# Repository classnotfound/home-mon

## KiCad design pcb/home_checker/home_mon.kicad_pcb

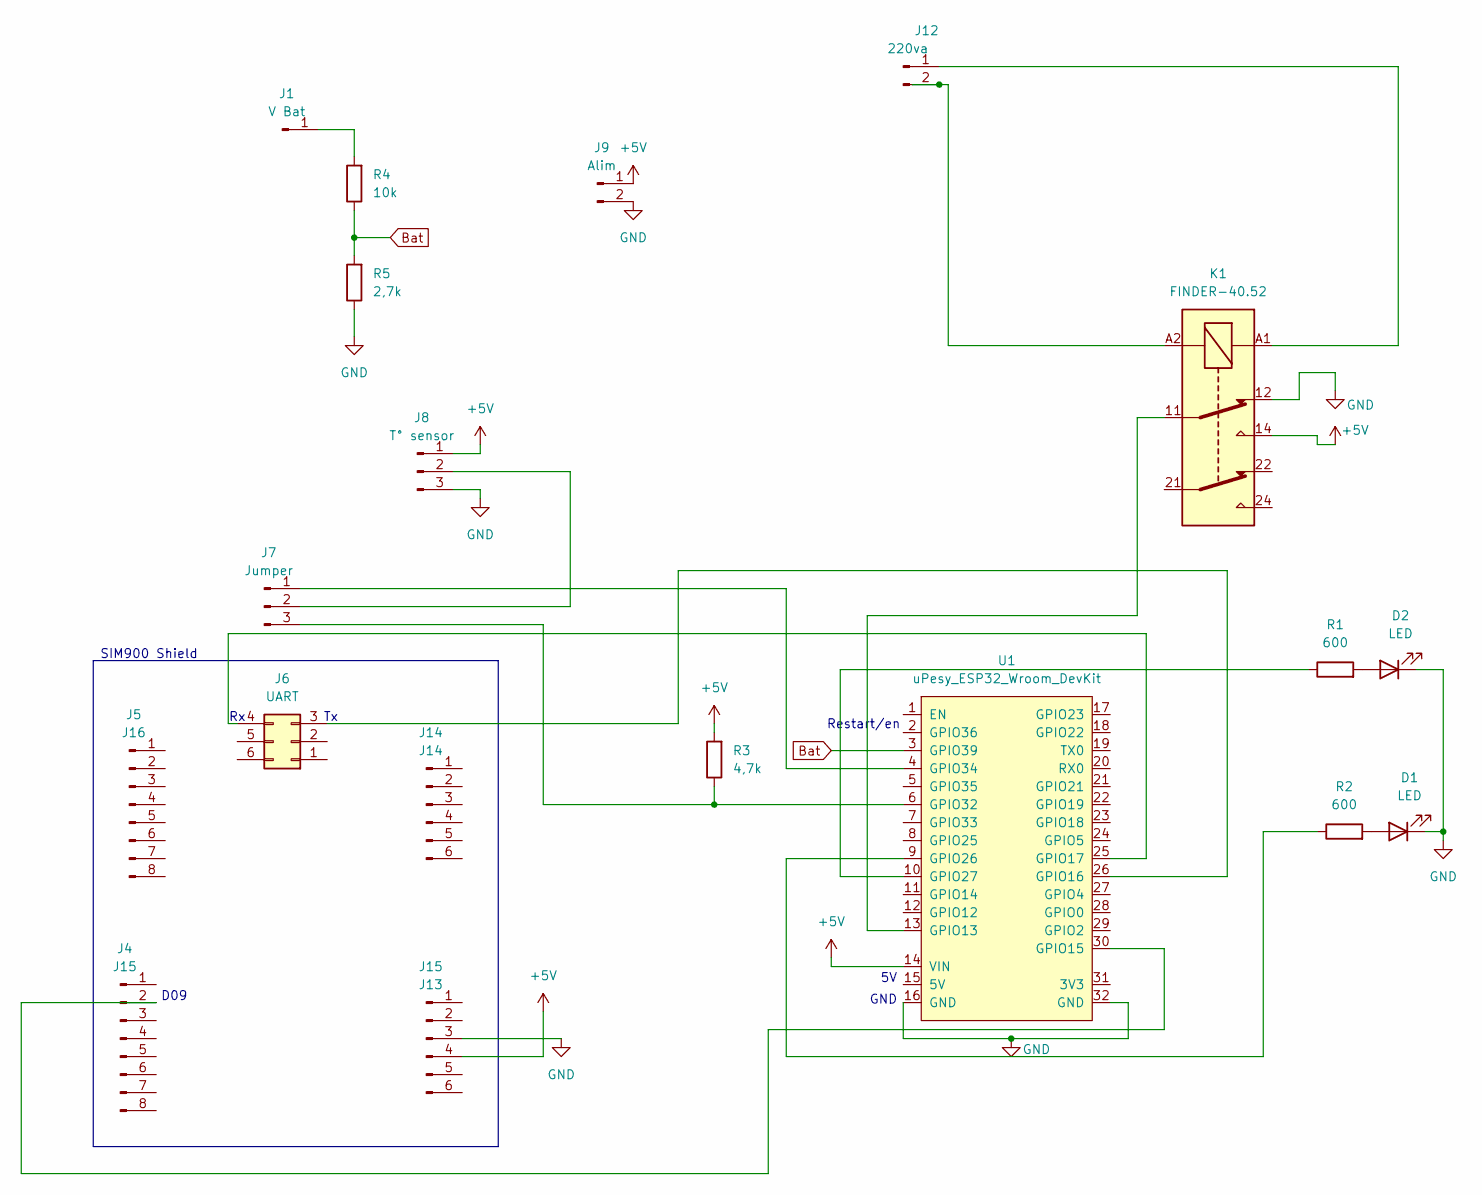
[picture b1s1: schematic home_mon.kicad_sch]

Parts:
D1, D2: LED; LED_D3.0mm
J1: V Bat; TestPoint_Loop_D1.80mm_Drill1.0mm_Beaded
J4: J15; PinHeader_1x08_P2.54mm_Vertical
J5: J16; PinHeader_1x08_P2.54mm_Vertical
J6: UART; PinHeader_2x03_P2.54mm_Vertical
J7: Jumper; PinHeader_1x03_P2.54mm_Vertical
J8: T° sensor; Samtec_HPM-03-01-x-S_Straight_1x03_Pitch5.08mm
J9: Alim; Samtec_HPM-02-01-x-S_Straight_1x02_Pitch5.08mm
J12: 220va; Samtec_HPM-02-01-x-S_Straight_1x02_Pitch5.08mm
J14: J14; PinHeader_1x06_P2.54mm_Vertical
J15: J13; PinHeader_1x06_P2.54mm_Vertical
K1: FINDER-40.52; Relay_DPDT_Finder_40.52
R1, R2: 600; R_Axial_DIN0207_L6.3mm_D2.5mm_P10.16mm_Horizontal
R3: 4,7k; R_Axial_DIN0207_L6.3mm_D2.5mm_P10.16mm_Horizontal
R4: 10k; R_Axial_DIN0207_L6.3mm_D2.5mm_P10.16mm_Horizontal
R5: 2,7k; R_Axial_DIN0207_L6.3mm_D2.5mm_P10.16mm_Horizontal
U1: uPesy_ESP32_Wroom_DevKit

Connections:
+5V: J8.1, J9.1, J15.4, K1.14, R3.2, U1.14 (VIN)
Bat: R4.1, R5.2, U1.3 (GPIO39)
GND: D1.1 (K), D2.1 (K), J8.3, J9.2, J15.3, K1.12, R5.1, U1.16 (GND), U1.32 (GND)
unnamed: D1.2 (A), R2.2
unnamed: D2.2 (A), R1.2
unnamed: J1.1, R4.2
unnamed: J4.2, U1.30 (GPIO15)
unnamed: J6.3, U1.26 (GPIO16)
unnamed: J6.4, U1.25 (GPIO17)
unnamed: J7.1, U1.4 (GPIO34)
unnamed: J7.2, J8.2
unnamed: J7.3, R3.1, U1.6 (GPIO32)
unnamed: J12.1, K1.A1
unnamed: J12.2, K1.A2
unnamed: K1.11, U1.13 (GPIO13)
unnamed: R2.1, U1.9 (GPIO26)
unnamed: R1.1, U1.10 (GPIO27)

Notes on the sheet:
Restart/en
D09
SIM900 Shield
GND

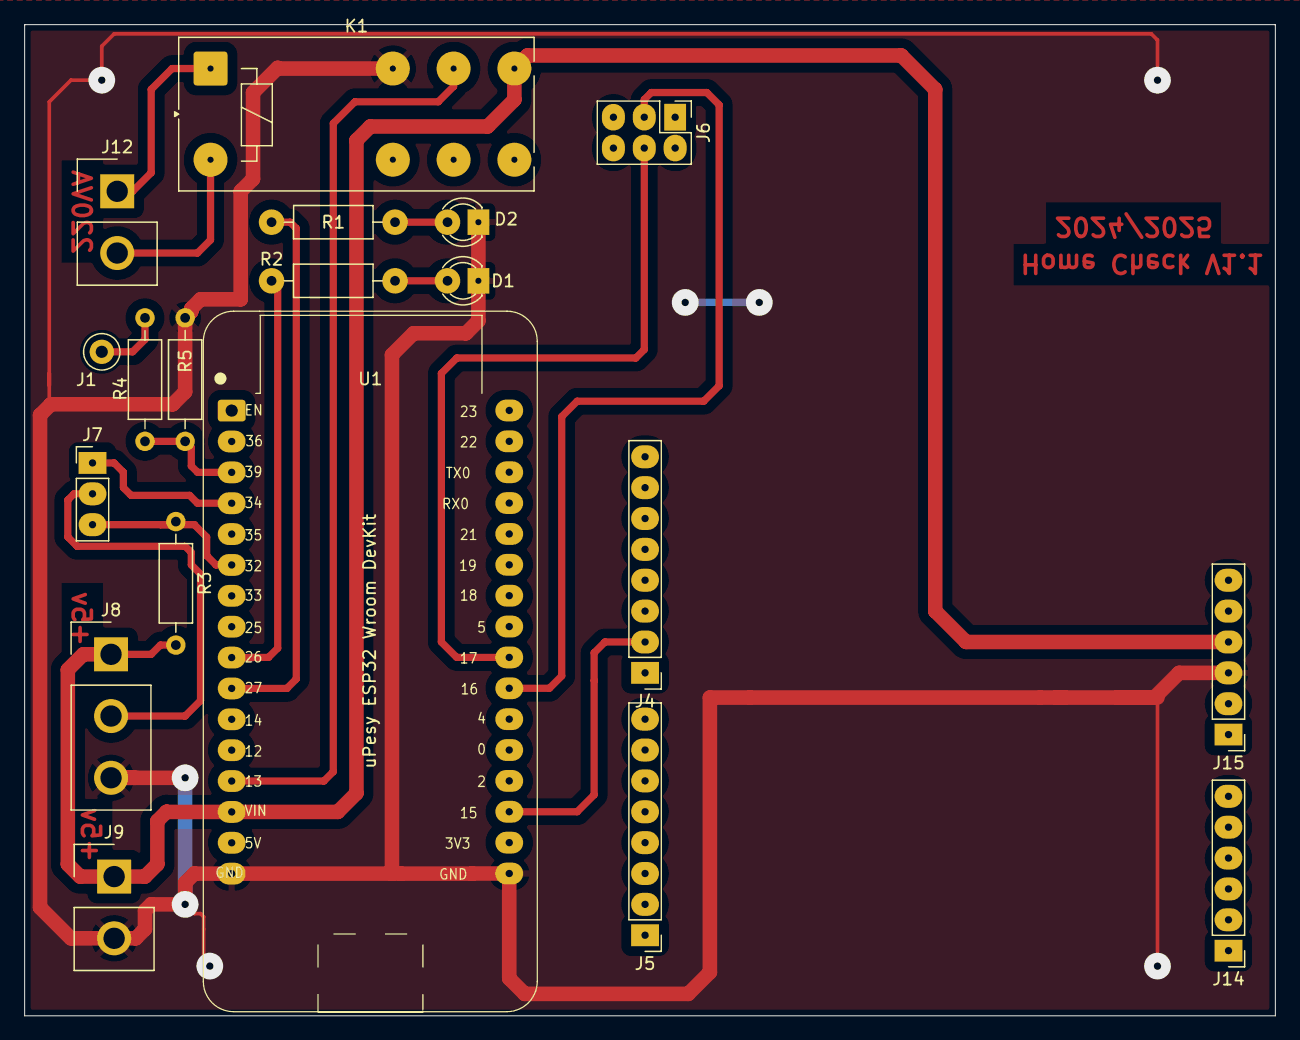
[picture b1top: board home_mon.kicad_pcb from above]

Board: 2 copper layers, 102.9 x 81.6 mm, 19 parts (0 on the bottom side), 17 nets.

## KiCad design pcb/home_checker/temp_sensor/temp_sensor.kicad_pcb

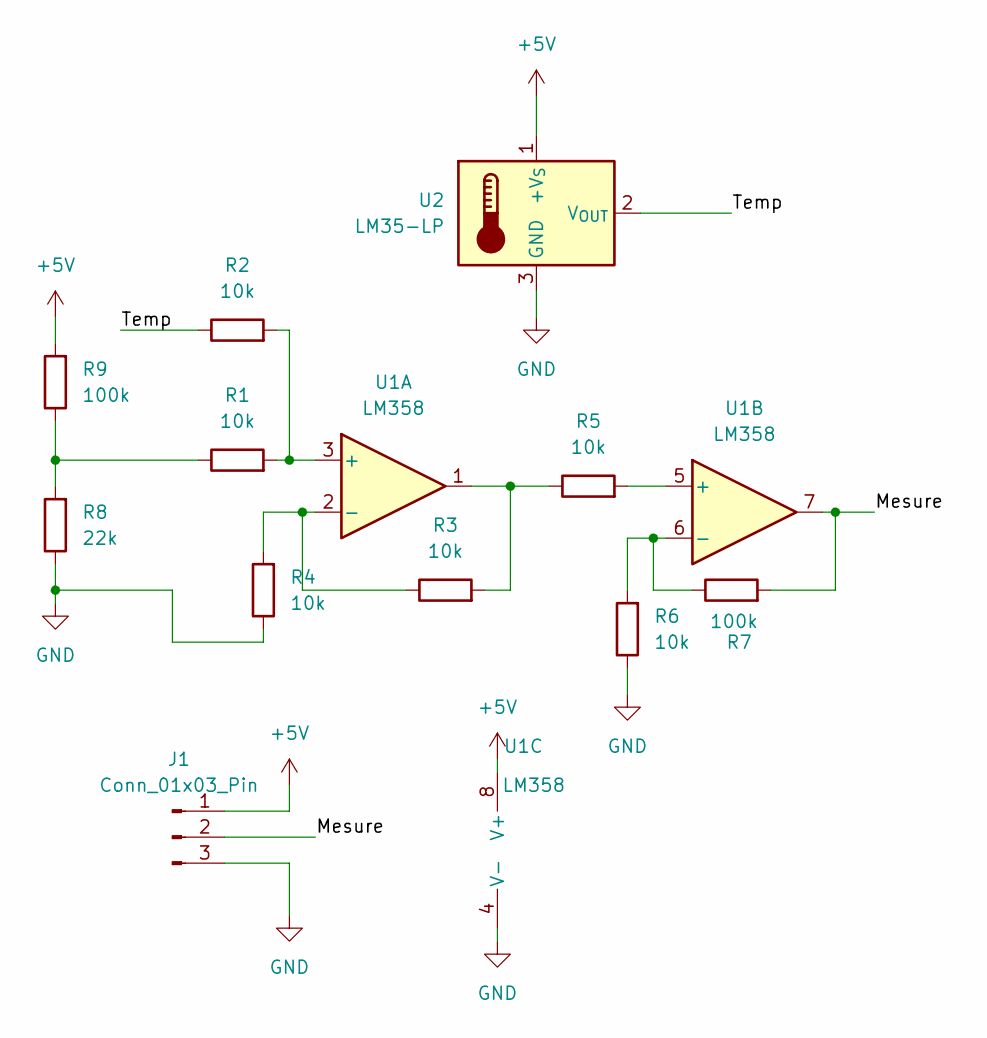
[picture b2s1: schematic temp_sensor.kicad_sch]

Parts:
J1: Conn_01x03_Pin; Samtec_HPM-03-01-x-S_Straight_1x03_Pitch5.08mm
R1, R2, R3, R4, R5, R6: 10k; R_Axial_DIN0207_L6.3mm_D2.5mm_P10.16mm_Horizontal
R7, R9: 100k; R_Axial_DIN0207_L6.3mm_D2.5mm_P10.16mm_Horizontal
R8: 22k; R_Axial_DIN0207_L6.3mm_D2.5mm_P10.16mm_Horizontal
U1: LM358; CERDIP-8_W7.62mm_SideBrazed_LongPads
U2: LM35-LP; TO-92_Inline

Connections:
+5V: J1.1, R9.2, U1.8 (V+), U2.1 (+V_{S})
/Mesure: J1.2, R7.2, U1.7
/Temp: R2.1, U2.2 (V_{OUT})
GND: J1.3, R4.1, R6.1, R8.1, U1.4 (V-), U2.3 (GND)
unnamed: R1.1, R8.2, R9.1
unnamed: R3.2, R5.1, U1.1
unnamed: R1.2, R2.2, U1.3 (+)
unnamed: R3.1, R4.2, U1.2 (-)
unnamed: R5.2, U1.5 (+)
unnamed: R6.2, R7.1, U1.6 (-)

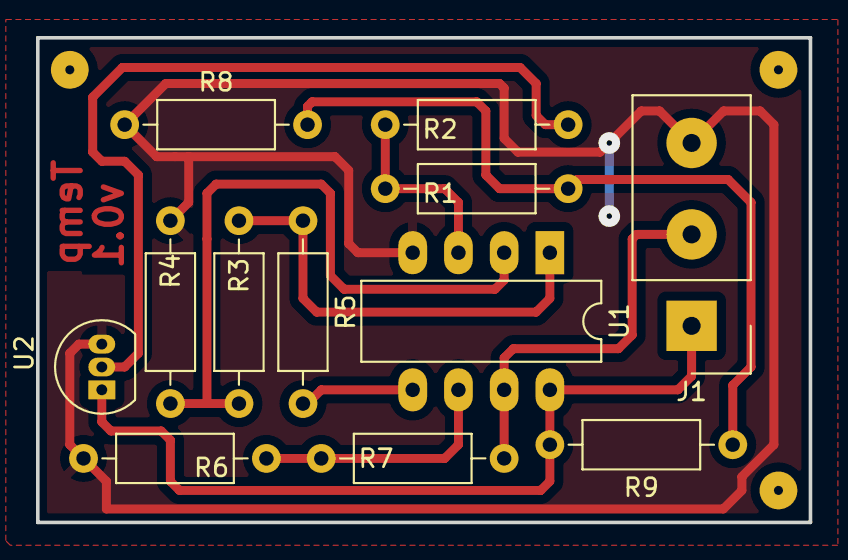
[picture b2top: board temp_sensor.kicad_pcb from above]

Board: 2 copper layers, 42.9 x 26.9 mm, 12 parts (0 on the bottom side), 10 nets.

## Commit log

2025-03-01 First version of the Home Monitor
2025-03-03 feat: Make implementation multiusers fix competition issues using semaphores make temperature alerting using averaged temperature instead of direct reading
2025-03-06 chore: Add gitignore
2025-03-06 feat: Monitor the battery voltage
2025-03-09 fix: Make the sending of sending operational again (canary exception) Make the ADC more reliable
2025-03-11 feat: Finalize battery voltage measurement add a reboot command
